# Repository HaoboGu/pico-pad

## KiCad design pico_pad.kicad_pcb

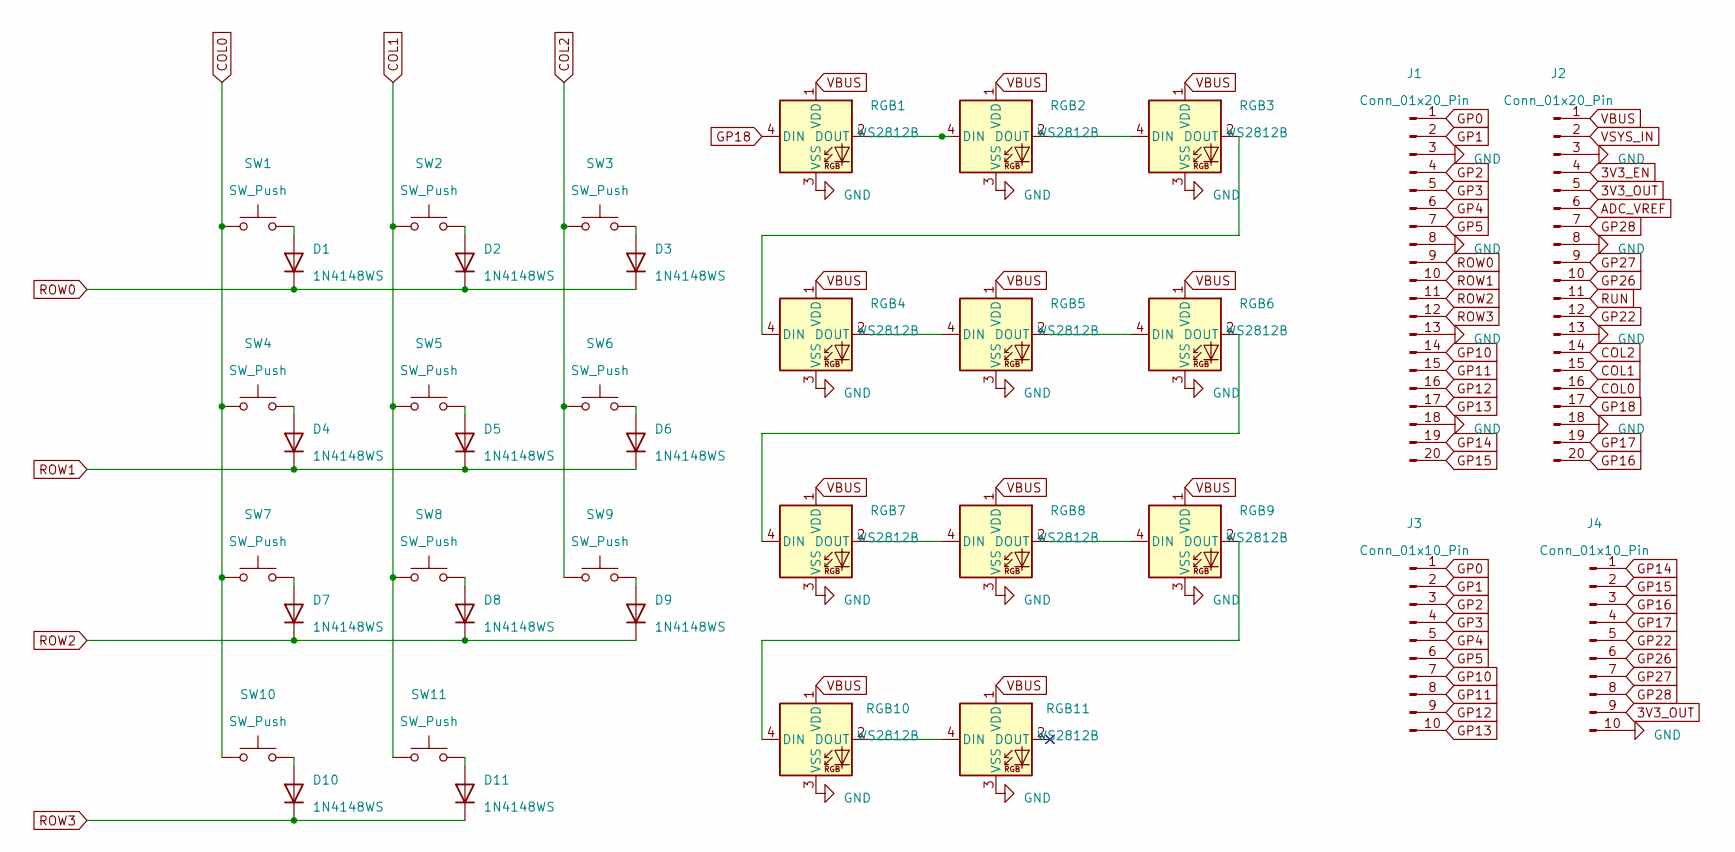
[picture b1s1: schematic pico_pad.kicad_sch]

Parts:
D1, D2, D3, D4, D5, D6, D7, D8, D9, D10, D11: 1N4148WS; D_SOD-123
J1, J2: Conn_01x20_Pin; PinSocket_1x20_P2.54mm_Vertical
J3, J4: Conn_01x10_Pin; PinSocket_1x10_P2.54mm_Vertical
RGB1, RGB2, RGB3, RGB4, RGB5, RGB6, RGB7, RGB8, RGB9, RGB10, RGB11: WS2812B; LED-SMD_L3.2-W2.8-BR_DY-S352818
SW1, SW2, SW3, SW4, SW5, SW6, SW7, SW8, SW9, SW11: SW_Push; SW_Hotswap_Kailh_MX_Plated_1.00u
SW10: SW_Push; SW_Hotswap_Kailh_MX_Plated_2.00u

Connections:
3V3_EN: J2.4
3V3_OUT: J2.5, J4.9
ADC_VREF: J2.6
COL0: J2.16, SW1.1, SW4.1, SW7.1, SW10.1
COL1: J2.15, SW2.1, SW5.1, SW8.1, SW11.1
COL2: J2.14, SW3.1, SW6.1, SW9.1
GND: J1.3, J1.8, J1.13, J1.18, J2.3, J2.8, J2.13, J2.18, J4.10, RGB1.3 (VSS), RGB2.3 (VSS), RGB3.3 (VSS), RGB4.3 (VSS), RGB5.3 (VSS), RGB6.3 (VSS), RGB7.3 (VSS), RGB8.3 (VSS), RGB9.3 (VSS), RGB10.3 (VSS), RGB11.3 (VSS)
GP0: J1.1, J3.1
GP1: J1.2, J3.2
GP2: J1.4, J3.3
GP3: J1.5, J3.4
GP4: J1.6, J3.5
GP5: J1.7, J3.6
GP10: J1.14, J3.7
GP11: J1.15, J3.8
GP12: J1.16, J3.9
GP13: J1.17, J3.10
GP14: J1.19, J4.1
GP15: J1.20, J4.2
GP16: J2.20, J4.3
GP17: J2.19, J4.4
GP18: J2.17, RGB1.4 (DIN)
GP22: J2.12, J4.5
GP26: J2.10, J4.6
GP27: J2.9, J4.7
GP28: J2.7, J4.8
unnamed: D1.2 (A), SW1.2
unnamed: D2.2 (A), SW2.2
unnamed: D3.2 (A), SW3.2
unnamed: D4.2 (A), SW4.2
unnamed: D5.2 (A), SW5.2
unnamed: D6.2 (A), SW6.2
unnamed: D7.2 (A), SW7.2
unnamed: D8.2 (A), SW8.2
unnamed: D9.2 (A), SW9.2
unnamed: D10.2 (A), SW10.2
unnamed: D11.2 (A), SW11.2
unnamed: RGB1.2 (DOUT), RGB2.4 (DIN)
unnamed: RGB2.2 (DOUT), RGB3.4 (DIN)
unnamed: RGB3.2 (DOUT), RGB4.4 (DIN)
unnamed: RGB4.2 (DOUT), RGB5.4 (DIN)
unnamed: RGB5.2 (DOUT), RGB6.4 (DIN)
unnamed: RGB6.2 (DOUT), RGB7.4 (DIN)
unnamed: RGB7.2 (DOUT), RGB8.4 (DIN)
unnamed: RGB8.2 (DOUT), RGB9.4 (DIN)
unnamed: RGB9.2 (DOUT), RGB10.4 (DIN)
unnamed: RGB10.2 (DOUT), RGB11.4 (DIN)
ROW0: D1.1 (K), D2.1 (K), D3.1 (K), J1.9
ROW1: D4.1 (K), D5.1 (K), D6.1 (K), J1.10
ROW2: D7.1 (K), D8.1 (K), D9.1 (K), J1.11
ROW3: D10.1 (K), D11.1 (K), J1.12
RUN: J2.11
VBUS: J2.1, RGB1.1 (VDD), RGB2.1 (VDD), RGB3.1 (VDD), RGB4.1 (VDD), RGB5.1 (VDD), RGB6.1 (VDD), RGB7.1 (VDD), RGB8.1 (VDD), RGB9.1 (VDD), RGB10.1 (VDD), RGB11.1 (VDD)
VSYS_IN: J2.2

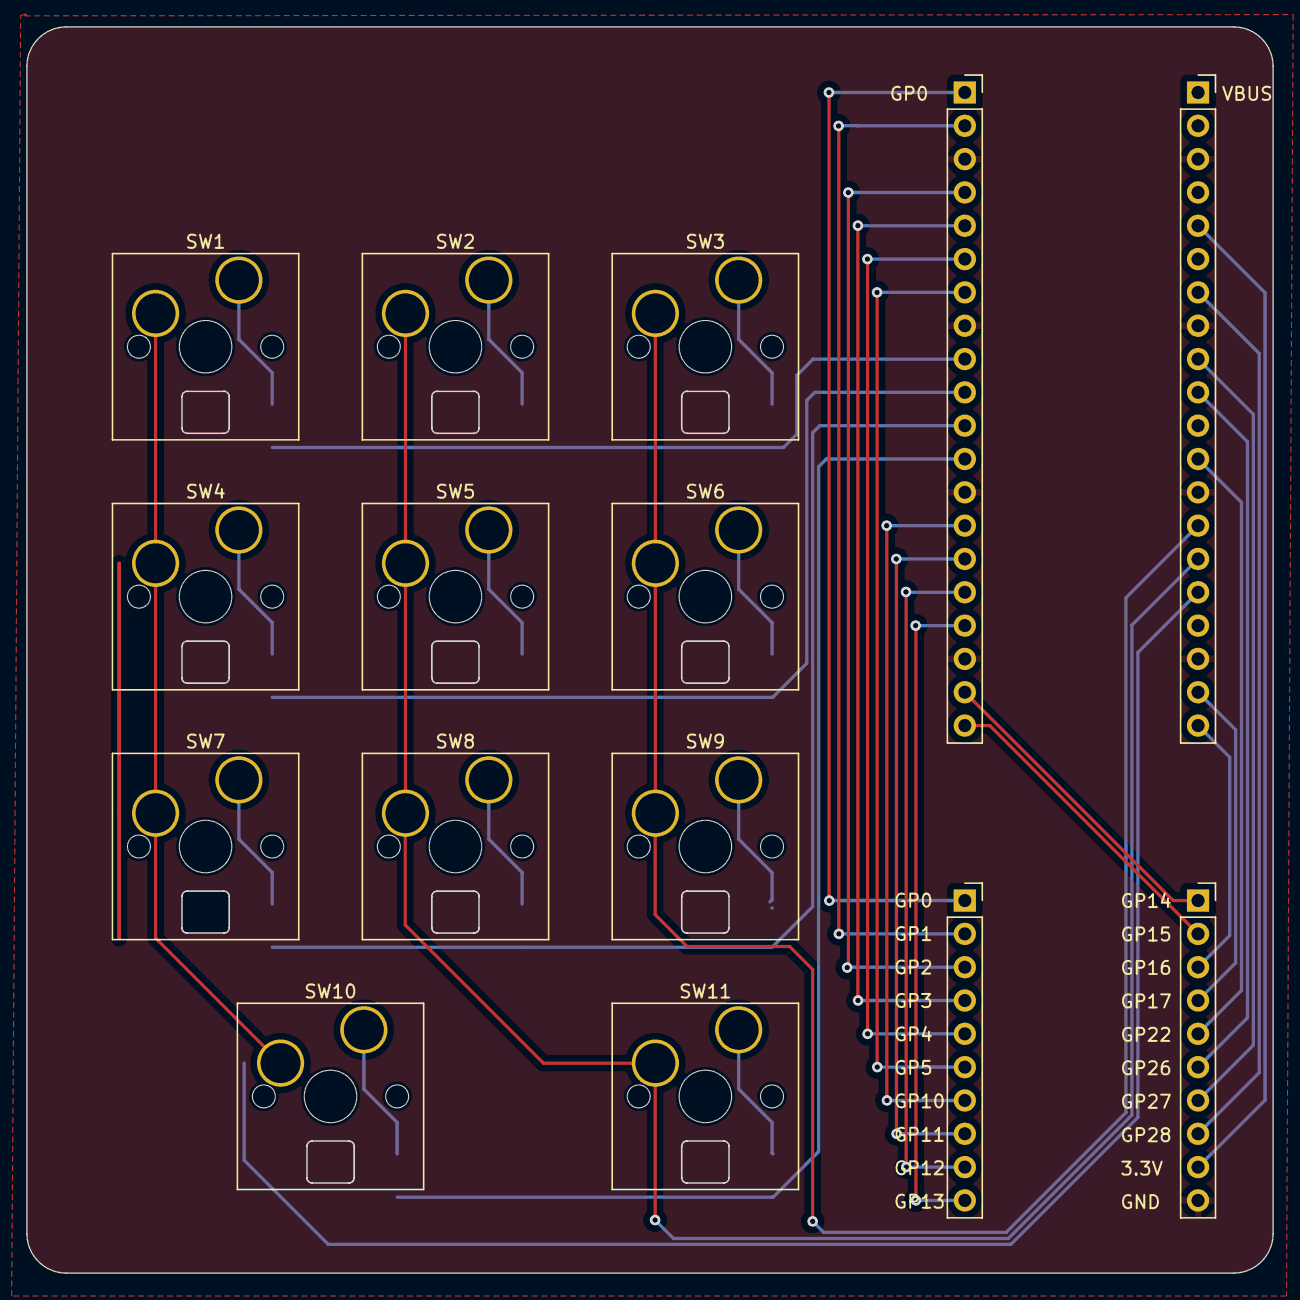
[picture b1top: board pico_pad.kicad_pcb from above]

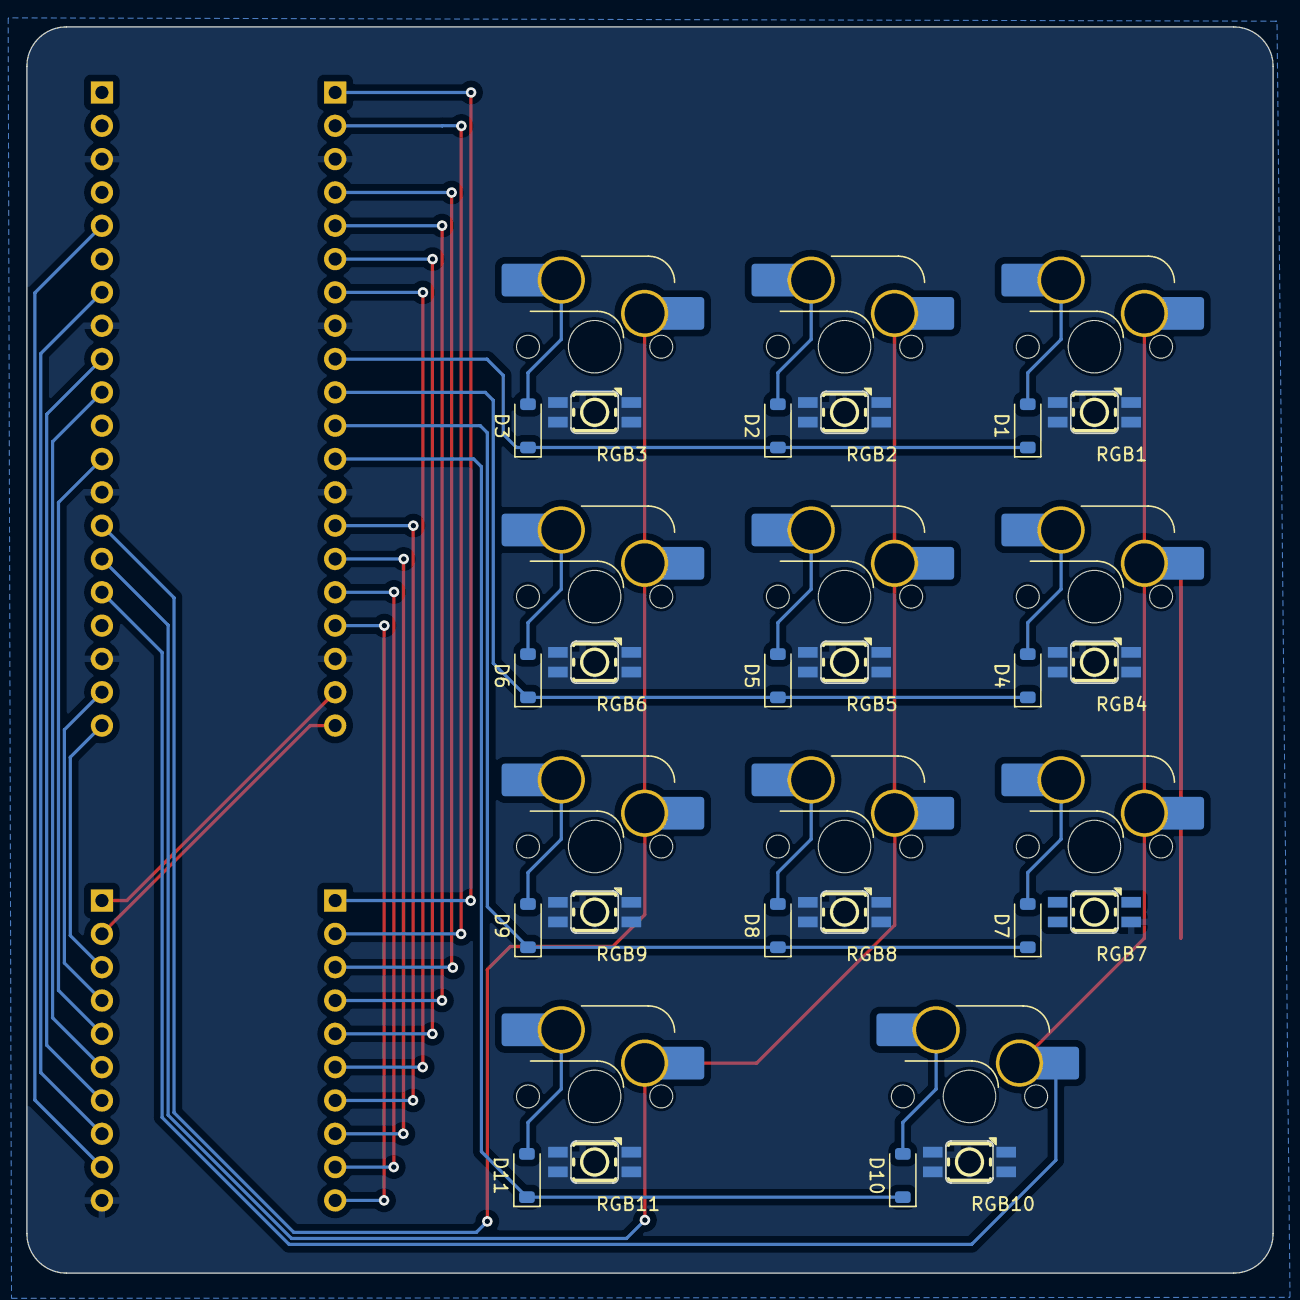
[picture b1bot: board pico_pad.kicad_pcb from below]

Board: 2 copper layers, 95.0 x 95.0 mm, 37 parts (22 on the bottom side), 50 nets.

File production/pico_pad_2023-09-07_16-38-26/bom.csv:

Designator,Footprint,Quantity,Value,LCSC Part #
"D1, D10, D11, D2, D3, D4, D5, D6, D7, D8, D9",D_SOD-323,11,1N4148WS,
"J1, J2",PinSocket_1x20_P2.54mm_Vertical,2,Conn_01x20_Pin,
"J3, J4",PinSocket_1x10_P2.54mm_Vertical,2,Conn_01x10_Pin,
"SW1, SW11, SW2, SW3, SW4, SW5, SW6, SW7, SW8, SW9",SW_Hotswap_Kailh_MX_Plated_1.00u,10,SW_Push,
SW10,SW_Hotswap_Kailh_MX_Plated_2.00u,1,SW_Push,

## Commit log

2023-09-07 add pico pad
2023-09-11 update project
2023-09-15 update pcb
2023-09-23 add kikit panelize config
2024-01-25 update pcb, add ws2812
